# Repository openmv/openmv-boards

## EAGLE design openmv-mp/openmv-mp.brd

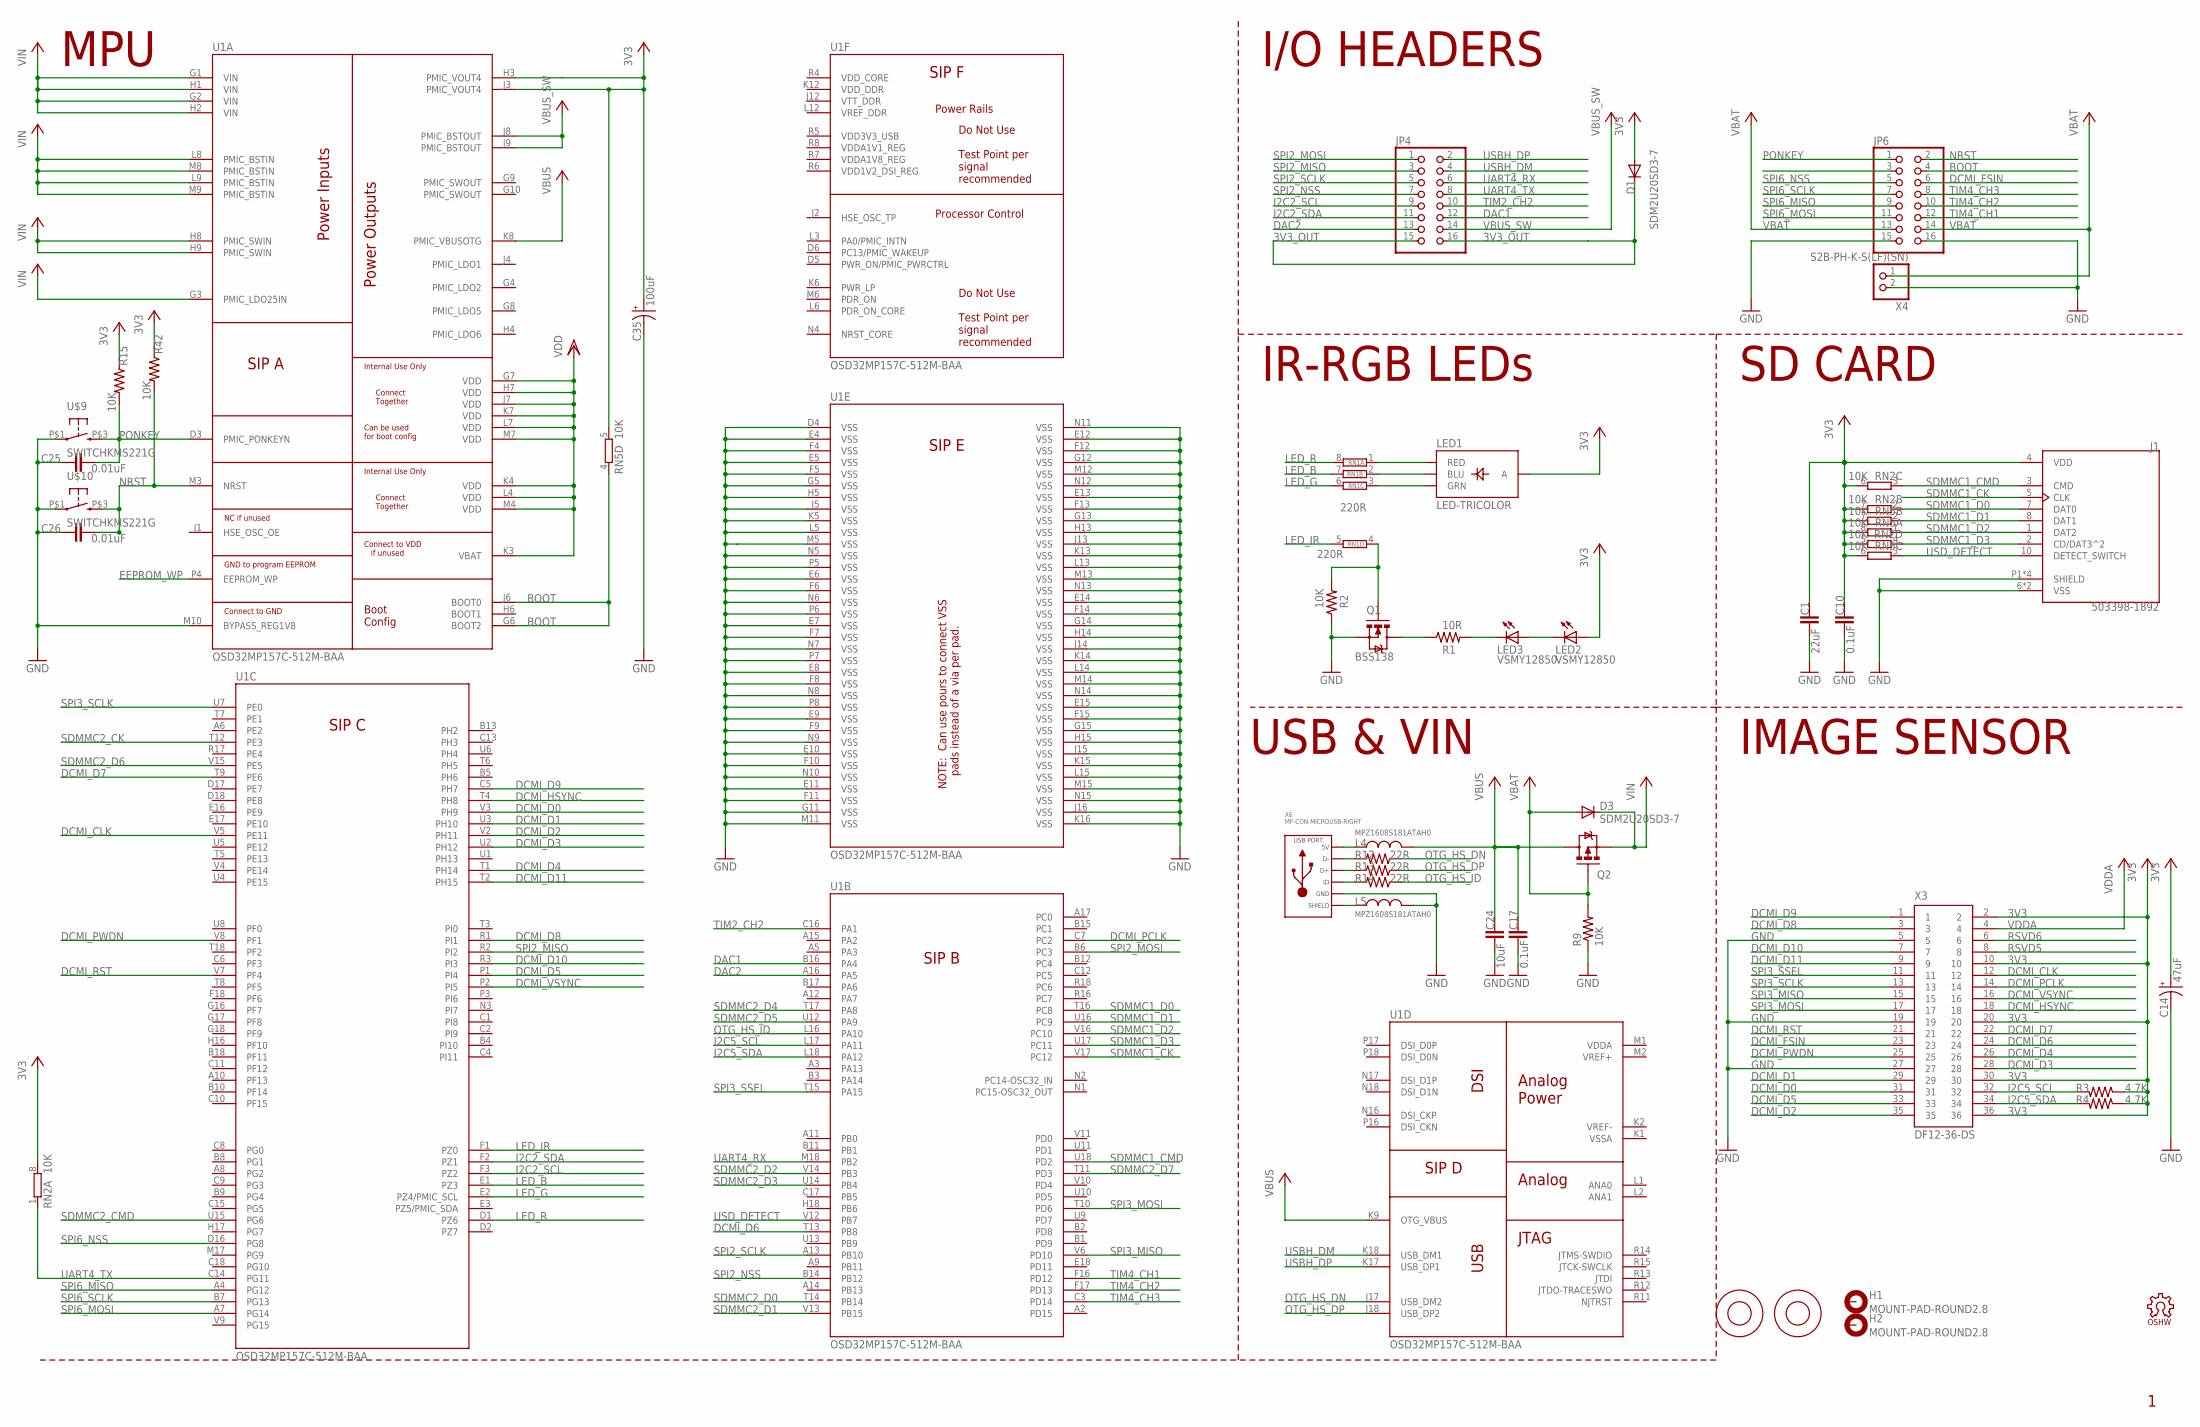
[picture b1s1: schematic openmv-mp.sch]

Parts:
C1: 22uF; 0805
C10, C17: 0.1uF; 0402-CAP
C14: 47uF; EIA3216
C24: 10uF; 0402-CAP
C25, C26: 0.01uF; 0402-CAP
C35: 100uF; EIA3216
D1, D3: SDM2U20SD3-7; SOD-323
H1, H2: MOUNT-PAD-ROUND2.8; 2,8-PAD
J1: 503398-1892; MOLEX_503398-1892
JP4, JP6: PINHD-2X8; 2X08
L4, L5: MPZ1608S181ATAH0; C0402
LED1: LED-TRICOLOR; LED-TRICOLOR-SMD-MF
LED2, LED3: VSMY12850; LED-1206
LOGO1: OSHW_LOGO_FILLX0100-NT; OSHW_FILLX100_NOTEXT
M1, M2: 9774030243R; 9774030151R
Q1: BSS138; SOT23-3
Q2: Si2301BDS; SOT23-3
R1: 10R; 0402-RES
R2, R9, R15, R42: 10K; 0402-RES
R3, R4: 4.7K; 0402-RES
R12, R13, R14: 22R; 0402-RES
RN1: 220R; EXBV8V
RN2, RN5: 10K; EXBV8V
U1: OSD32MP157C-512M-BAA; OSD32MP15X-BGA-324
U$9, U$10: SWITCHKMS221G; KMS221G
X3: DF12-36-DS
X4: S2B-PH-K-S(LF)(SN); JST-PH-2-THM-RA
X6: MF-CON-MICROUSB-RIGHT; MICROUSB-RIGHT

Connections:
3V3: C1.1, C10.1, C14.A (+), C35.A (+), D1.2 (A), J1.4 (VDD), LED1.A, LED2.A, R3.1, R4.1, R15.1, R42.1, RN2.5 (2), RN2.6 (2), RN2.7 (2), RN2.8 (2), RN5.5 (2), RN5.6 (2), RN5.7 (2), RN5.8 (2), U1.H3 (PMIC_VOUT4), U1.J3 (PMIC_VOUT4), X3.2, X3.10, X3.20, X3.30, X3.36
3V3_OUT: D1.1 (C), JP4.15, JP4.16
BOOT: JP6.4, RN5.4 (1), U1.G6 (BOOT2), U1.J6 (BOOT0)
DAC1: JP4.12, U1.B16 (PA4)
DAC2: JP4.13, U1.A16 (PA5)
DCMI_CLK: U1.V5 (PE11), X3.12
DCMI_D0: U1.V3 (PH9), X3.31
DCMI_D1: U1.U3 (PH10), X3.29
DCMI_D2: U1.V2 (PH11), X3.35
DCMI_D3: U1.U2 (PH12), X3.28
DCMI_D4: U1.T1 (PH14), X3.26
DCMI_D5: U1.P1 (PI4), X3.33
DCMI_D6: U1.T13 (PB8), X3.24
DCMI_D7: U1.T9 (PE6), X3.22
DCMI_D8: U1.R1 (PI1), X3.3
DCMI_D9: U1.C5 (PH7), X3.1
DCMI_D10: U1.R3 (PI3), X3.7
DCMI_D11: U1.T2 (PH15), X3.9
DCMI_FSIN: JP6.6, X3.23
DCMI_HSYNC: U1.T4 (PH8), X3.18
DCMI_PCLK: U1.C7 (PC2), X3.14
DCMI_PWDN: U1.V8 (PF1), X3.25
DCMI_RST: U1.V7 (PF4), X3.21
DCMI_VSYNC: U1.P2 (PI5), X3.16
EEPROM_WP: U1.P4 (EEPROM_WP)
GND: C1.2, C10.2, C14.C (-), C17.2, C24.2, C25.2, C26.2, C35.C (-), J1.6 (VSS), J1.9 (VSS), J1.P1 (SHIELD), J1.P2 (SHIELD), J1.P3 (SHIELD), J1.P4 (SHIELD), JP6.15, JP6.16, L5.2, Q1.2 (S), R2.1, R9.1, U1.D4 (VSS), U1.E4 (VSS), U1.E5 (VSS), U1.E6 (VSS), U1.E7 (VSS), U1.E8 (VSS), U1.E9 (VSS), U1.E10 (VSS), U1.E11 (VSS), U1.E12 (VSS), U1.E13 (VSS), U1.E14 (VSS), U1.E15 (VSS), U1.F4 (VSS), U1.F5 (VSS), U1.F6 (VSS), U1.F7 (VSS), U1.F8 (VSS), U1.F9 (VSS), U1.F10 (VSS), U1.F11 (VSS), U1.F12 (VSS), U1.F13 (VSS), U1.F14 (VSS), U1.F15 (VSS), U1.G5 (VSS), U1.G11 (VSS), U1.G12 (VSS), U1.G13 (VSS), U1.G14 (VSS), U1.G15 (VSS), U1.H5 (VSS), U1.H13 (VSS), U1.H14 (VSS), U1.H15 (VSS), U1.J5 (VSS), U1.J13 (VSS), U1.J14 (VSS), U1.J15 (VSS), U1.J16 (VSS), U1.K5 (VSS), U1.K13 (VSS), U1.K14 (VSS), U1.K15 (VSS), U1.K16 (VSS), U1.L5 (VSS), U1.L13 (VSS), U1.L14 (VSS), U1.L15 (VSS), U1.M5 (VSS), U1.M10 (BYPASS_REG1V8), U1.M11 (VSS), U1.M12 (VSS), U1.M13 (VSS), U1.M14 (VSS), U1.M15 (VSS), U1.N5 (VSS), U1.N6 (VSS), U1.N7 (VSS), U1.N8 (VSS), U1.N9 (VSS), U1.N10 (VSS), U1.N11 (VSS), U1.N12 (VSS), U1.N13 (VSS), U1.N14 (VSS), U1.N15 (VSS), U1.P5 (VSS), U1.P6 (VSS), U1.P7 (VSS), U1.P8 (VSS), U$9.P$1 (1), U$10.P$1 (1), X3.5, X3.19, X3.27, X4.2 (1), X6.5 (GND)
I2C2_SCL: JP4.9, U1.F3 (PZ2)
I2C2_SDA: JP4.11, U1.F2 (PZ1)
I2C5_SCL: R3.2, U1.L17 (PA11), X3.32
I2C5_SDA: R4.2, U1.L18 (PA12), X3.34
LED_B: RN1.7 (2), U1.E1 (PZ3)
LED_G: RN1.6 (2), U1.E2 (PZ4/PMIC_SCL)
LED_IR: RN1.5 (2), U1.F1 (PZ0)
LED_R: RN1.8 (2), U1.D1 (PZ6)
unnamed: Q1.1 (G), R2.2, RN1.4 (1)
unnamed: LED1.B (BLU), RN1.2 (1)
unnamed: LED1.R (RED), RN1.1
unnamed: LED1.G (GRN), RN1.3 (1)
unnamed: LED3.C, R1.2
unnamed: Q1.3 (D), R1.1
unnamed: LED2.C, LED3.A
unnamed: L4.1, X6.1 (5V)
unnamed: R12.2, X6.2 (D-)
unnamed: R13.2, X6.3 (D+)
unnamed: R14.2, X6.4 (ID)
unnamed: L5.1, X6.S1 (SLD), X6.S2 (SLD), X6.S3 (SLD), X6.S4 (SLD), X6.S5 (SLD), X6.S6 (SLD)
NRST: C26.1, JP6.2, R42.2, U1.M3 (NRST), U$10.P$3 (2)
OTG_HS_DN: R12.1, U1.J17 (USB_DM2)
OTG_HS_DP: R13.1, U1.J18 (USB_DP2)
OTG_HS_ID: R14.1, U1.L16 (PA10)
PONKEY: C25.1, JP6.1, R15.2, U1.D3 (PMIC_PONKEYN), U$9.P$3 (2)
RSVD5: X3.8
RSVD6: X3.6
SDMMC1_CK: J1.5 (CLK), U1.V17 (PC12)
SDMMC1_CMD: J1.3 (CMD), RN2.3 (1), U1.U18 (PD2)
SDMMC1_D0: J1.7 (DAT0), RN2.2 (1), U1.T16 (PC8)
SDMMC1_D1: J1.8 (DAT1), RN5.2 (1), U1.U16 (PC9)
SDMMC1_D2: J1.1 (DAT2), RN5.1, U1.V16 (PC10)
SDMMC1_D3: J1.2 (CD/DAT3^2), RN2.4 (1), U1.U17 (PC11)
SDMMC2_CK: U1.T12 (PE3)
SDMMC2_CMD: U1.U15 (PG6)
SDMMC2_D0: U1.T14 (PB14)
SDMMC2_D1: U1.V13 (PB15)
SDMMC2_D2: U1.V14 (PB3)
SDMMC2_D3: U1.U14 (PB4)
SDMMC2_D4: U1.T17 (PA8)
SDMMC2_D5: U1.U12 (PA9)
SDMMC2_D6: U1.V15 (PE5)
SDMMC2_D7: U1.T11 (PD3)
SPI2_MISO: JP4.3, U1.R2 (PI2)
SPI2_MOSI: JP4.1, U1.B6 (PC3)
SPI2_NSS: JP4.7, U1.B14 (PB12)
SPI2_SCLK: JP4.5, U1.A13 (PB10)
SPI3_MISO: U1.V6 (PD10), X3.15
SPI3_MOSI: U1.T10 (PD6), X3.17
SPI3_SCLK: U1.U7 (PE0), X3.13
SPI3_SSEL: U1.T15 (PA15), X3.11
SPI6_MISO: JP6.9, U1.A4 (PG12)
SPI6_MOSI: JP6.11, U1.A7 (PG14)
SPI6_NSS: JP6.5, U1.D16 (PG8)
SPI6_SCLK: JP6.7, U1.B7 (PG13)
TIM2_CH2: JP4.10, U1.C16 (PA1)
TIM4_CH1: JP6.12, U1.F16 (PD12)
TIM4_CH2: JP6.10, U1.F17 (PD13)
TIM4_CH3: JP6.8, U1.C3 (PD14)
UART4_RX: JP4.6, U1.M18 (PB2)
UART4_TX: JP4.8, RN2.1, U1.C14 (PG11)
USBH_DM: JP4.4, U1.K18 (USB_DM1)
USBH_DP: JP4.2, U1.K17 (USB_DP1)
USD_DETECT: J1.10 (DETECT_SWITCH), RN5.3 (1), U1.V12 (PB7)
VBAT: D3.2 (A), JP6.13, JP6.14, Q2.1 (G), R9.2, X4.1 (2)
VBUS: C17.1, C24.1, L4.2, Q2.3 (D), U1.K8 (PMIC_VBUSOTG), U1.K9 (OTG_VBUS)
VBUS_SW: JP4.14, U1.J8 (PMIC_BSTOUT), U1.J9 (PMIC_BSTOUT)
VDD: U1.G7 (VDD), U1.H7 (VDD), U1.J7 (VDD), U1.K3 (VBAT), U1.K4 (VDD), U1.K7 (VDD), U1.L4 (VDD), U1.L7 (VDD), U1.M4 (VDD), U1.M7 (VDD)
VDDA: X3.4
VIN: D3.1 (C), Q2.2 (S), U1.G1 (VIN), U1.G2 (VIN), U1.G3 (PMIC_LDO25IN), U1.H1 (VIN), U1.H2 (VIN), U1.H8 (PMIC_SWIN), U1.H9 (PMIC_SWIN), U1.L8 (PMIC_BSTIN), U1.L9 (PMIC_BSTIN), U1.M8 (PMIC_BSTIN), U1.M9 (PMIC_BSTIN)

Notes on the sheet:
SD CARD
IMAGE SENSOR
IR-RGB LEDs
MPU
I/O HEADERS
USB & VIN

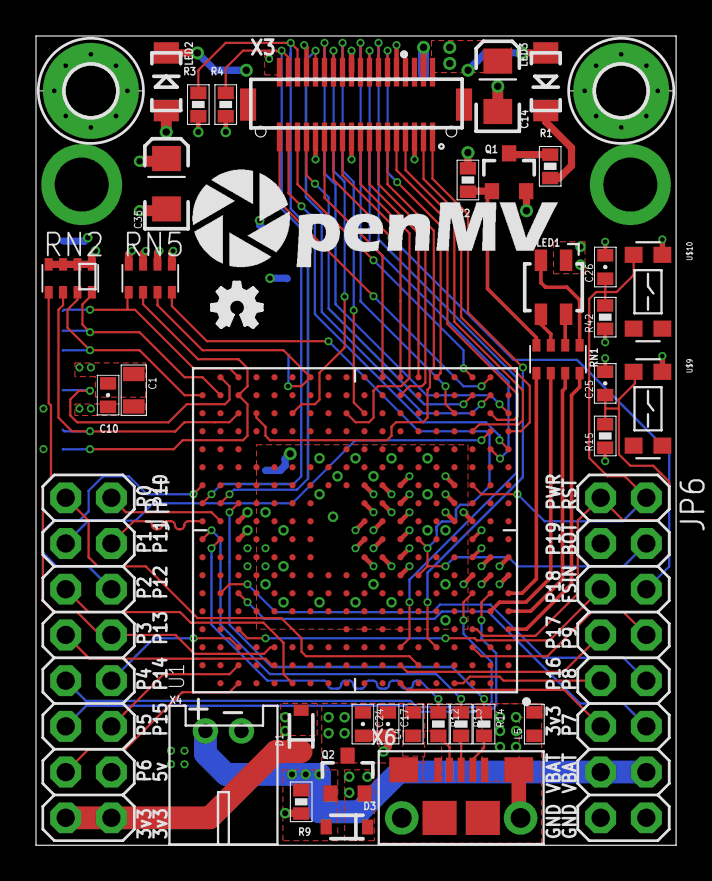
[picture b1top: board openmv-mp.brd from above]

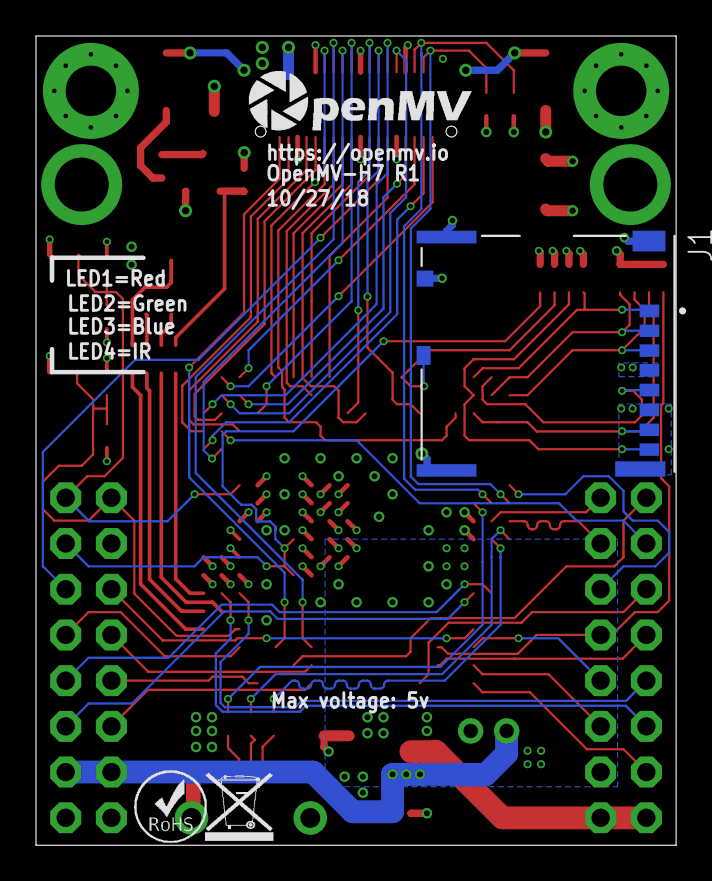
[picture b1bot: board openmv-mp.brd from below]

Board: 4 copper layers, 35.6 x 45.0 mm, 48 parts (4 on the bottom side), 82 nets.

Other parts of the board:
U$1: WEEE
U$2: ROHS
U$3: OMV-LOGO
U$6: OMV-LOGO-BIG

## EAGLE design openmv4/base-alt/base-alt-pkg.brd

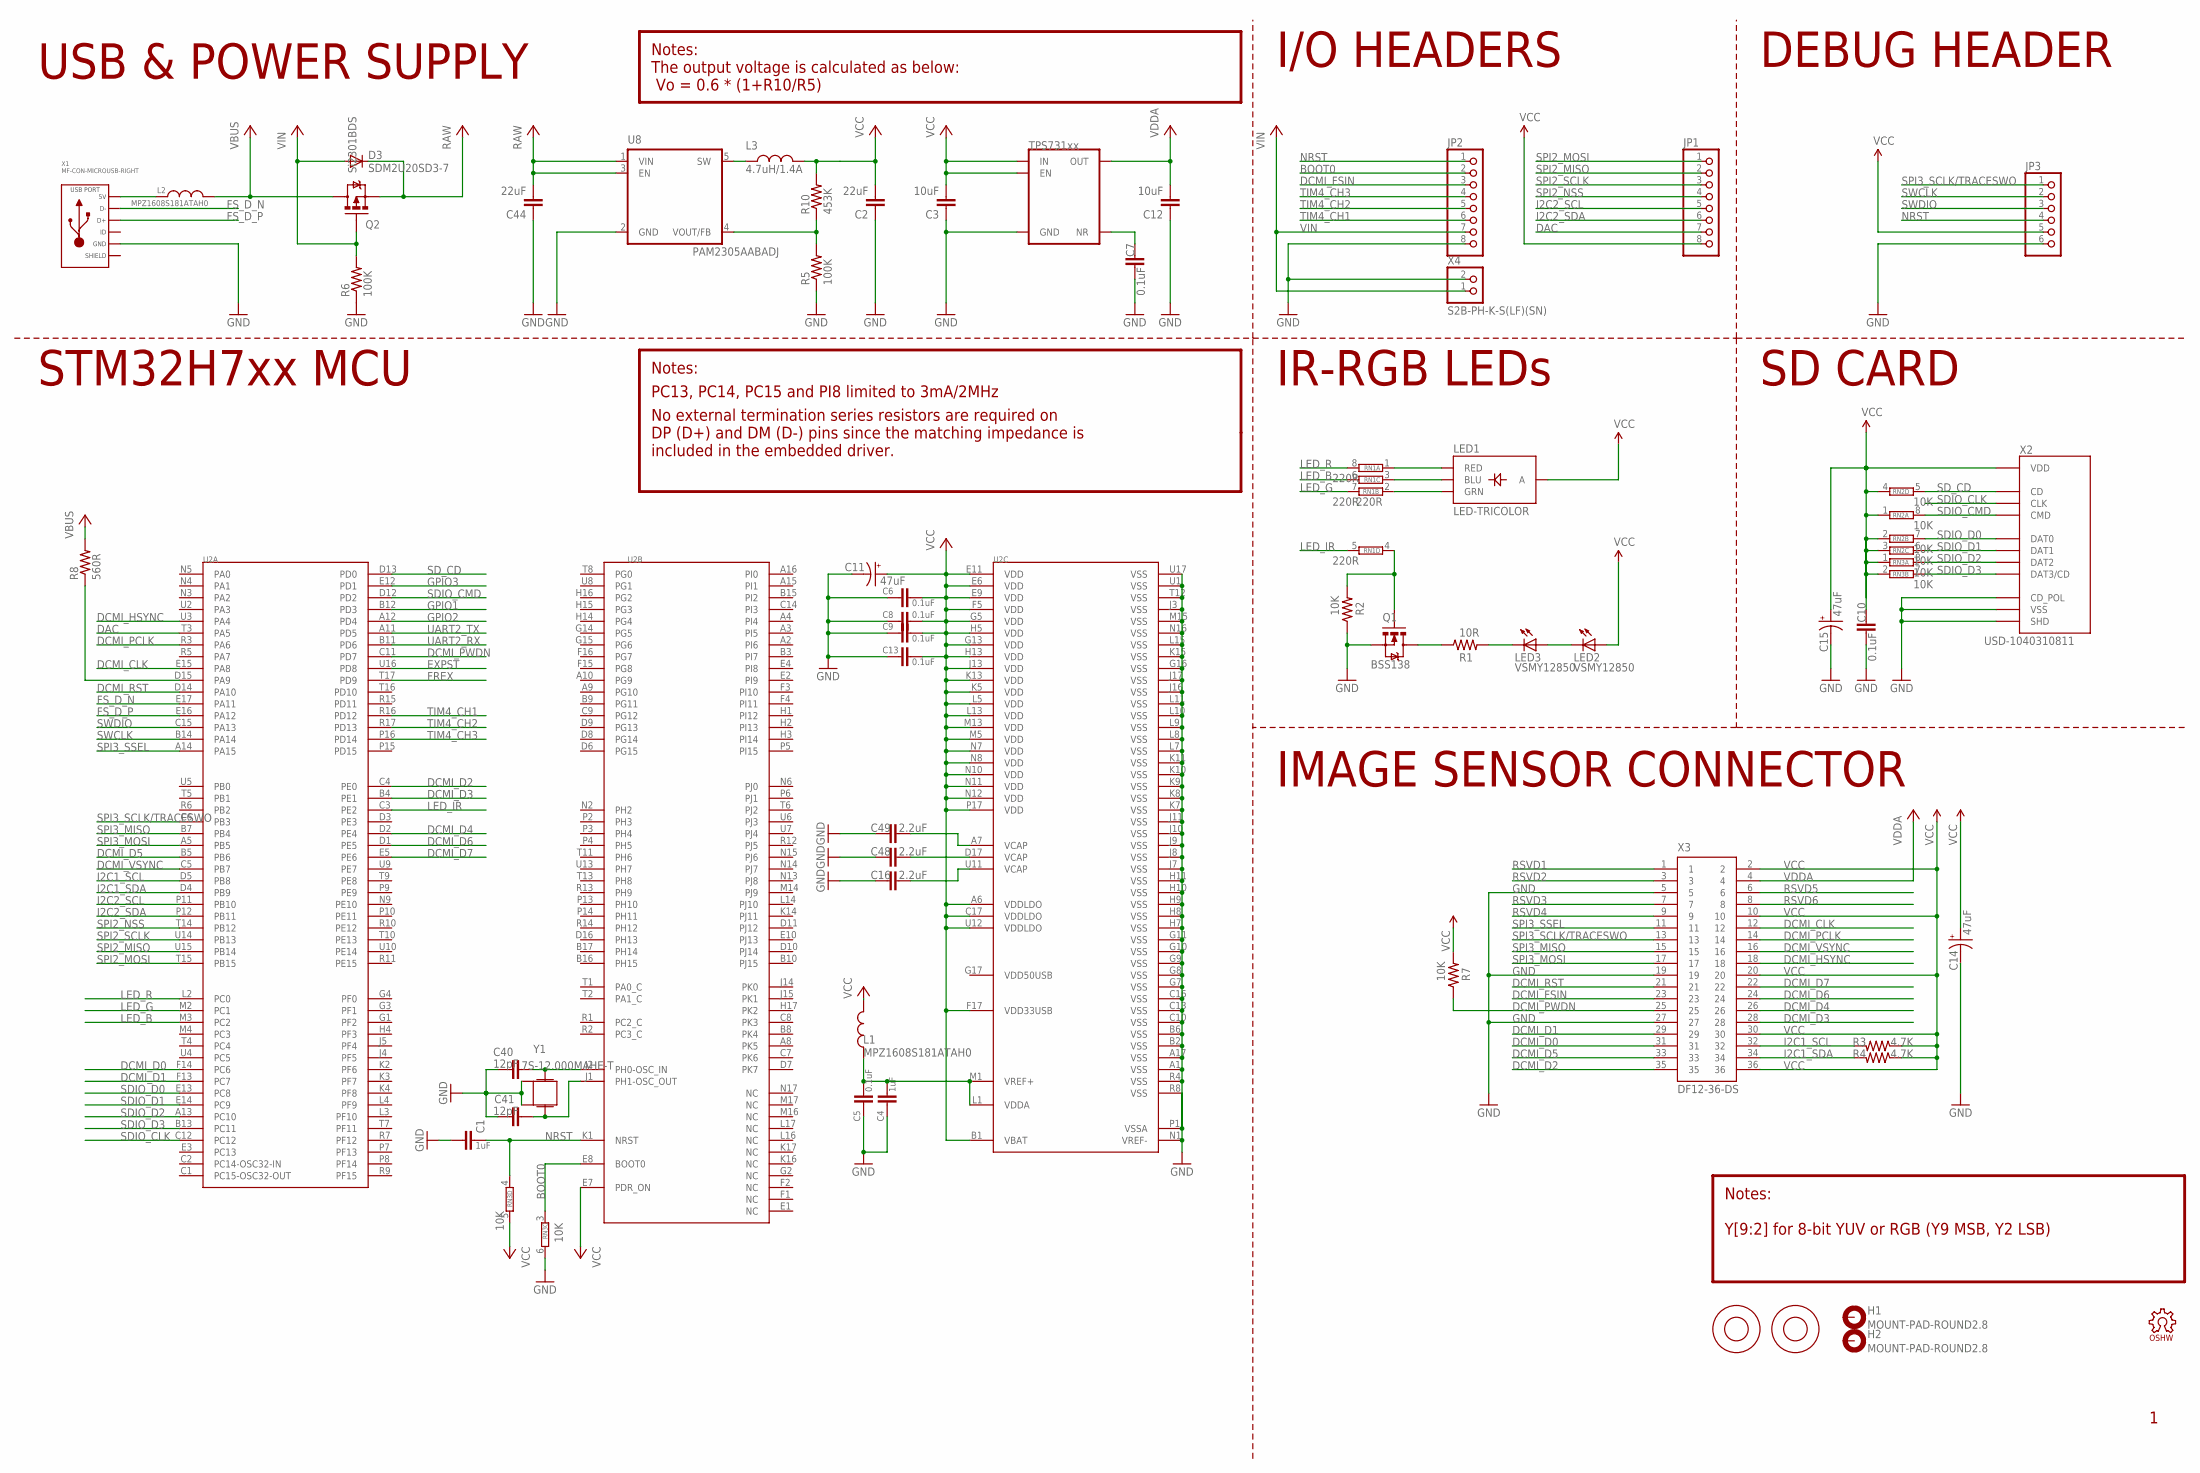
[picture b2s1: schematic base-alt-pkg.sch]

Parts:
C1, C4: 1uF; 0603-CAP
C2, C44: 22uF; 0805
C3, C12: 10uF; 0805
C5, C6, C7, C8, C9, C10, C13: 0.1uF; 0603-CAP
C11, C14, C15: 47uF; EIA3216
C16, C48, C49: 2.2uF; 0603-CAP
C40, C41: 12pF; 0603-CAP
D3: SDM2U20SD3-7; SOD-323
H1, H2: MOUNT-PAD-ROUND2.8; 2,8-PAD
JP1, JP2: PINHD-1X8; 1X08
JP3: PINHD-1X6; 1X06
L1, L2: MPZ1608S181ATAH0; 0603
L3: 4.7uH/1.4A; 1007
LED1: LED-TRICOLOR; LED-TRICOLOR-SMD-MF
LED2, LED3: VSMY12850; LED-1206
LOGO1: OSHW_LOGO_FILLX0100-NT; OSHW_FILLX100_NOTEXT
M1, M2: 9774030243R; 9774030151R
Q1: BSS138; SOT23-3
Q2: Si2301BDS; SOT23-3
R1: 10R; 0603-RES
R2, R7: 10K; 0603-RES
R3, R4: 4.7K; 0603-RES
R5, R6: 100K; 0603-RES
R8: 560R; 0603-RES
R10: 453K; 0603-RES
RN1: 220R; EXBV8V
RN2, RN3: 10K; EXBV8V
U2: STM32H743XIH6; TFBGA240+25
U5: TPS731XX; SOT23-5
U8: PAM2305AABADJ; TSOT25
X1: MF-CON-MICROUSB-RIGHT; MICROUSB-RIGHT
X2: USD-1040310811; 1040310811
X3: DF12-36-DS
X4: S2B-PH-K-S(LF)(SN); JST-PH-2-THM-RA
Y1: 7S-12.000MAHE-T; CRYSTAL-2.5X2.0

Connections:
BOOT0: JP2.2, RN3.3 (1), U2.E8 (BOOT0)
DAC: JP1.7, U2.T3 (PA5)
DCMI_CLK: U2.E15 (PA8), X3.12
DCMI_D0: U2.F14 (PC6), X3.31
DCMI_D1: U2.F13 (PC7), X3.29
DCMI_D2: U2.C4 (PE0), X3.35
DCMI_D3: U2.B4 (PE1), X3.28
DCMI_D4: U2.D2 (PE4), X3.26
DCMI_D5: U2.B5 (PB6), X3.33
DCMI_D6: U2.D1 (PE5), X3.24
DCMI_D7: U2.E5 (PE6), X3.22
DCMI_FSIN: JP2.3, X3.23
DCMI_HSYNC: U2.U3 (PA4), X3.18
DCMI_PCLK: U2.R3 (PA6), X3.14
DCMI_PWDN: R7.1, U2.C11 (PD7), X3.25
DCMI_RST: U2.D14 (PA10), X3.21
DCMI_VSYNC: U2.C5 (PB7), X3.16
EXPST: U2.U16 (PD8)
FREX: U2.T17 (PD9)
FS_D_N: U2.E17 (PA11), X1.2 (D-)
FS_D_P: U2.E16 (PA12), X1.3 (D+)
GND: C1.2, C2.1, C3.1, C4.2, C5.2, C6.2, C7.2, C8.2, C9.2, C10.2, C11.C (-), C12.1, C13.2, C14.C (-), C15.C (-), C16.2, C40.1, C41.1, C44.1, C48.2, C49.2, JP2.8, JP3.6, Q1.2 (S), R2.1, R5.1, R6.1, RN3.6 (2), U2.A1 (VSS), U2.A17 (VSS), U2.B2 (VSS), U2.B6 (VSS), U2.C10 (VSS), U2.C13 (VSS), U2.C16 (VSS), U2.G7 (VSS), U2.G8 (VSS), U2.G9 (VSS), U2.G10 (VSS), U2.G11 (VSS), U2.G16 (VSS), U2.H7 (VSS), U2.H8 (VSS), U2.H9 (VSS), U2.H10 (VSS), U2.H11 (VSS), U2.J3 (VSS), U2.J7 (VSS), U2.J8 (VSS), U2.J9 (VSS), U2.J10 (VSS), U2.J11 (VSS), U2.J16 (VSS), U2.J17 (VSS), U2.K7 (VSS), U2.K8 (VSS), U2.K9 (VSS), U2.K10 (VSS), U2.K11 (VSS), U2.K15 (VSS), U2.L7 (VSS), U2.L8 (VSS), U2.L9 (VSS), U2.L10 (VSS), U2.L11 (VSS), U2.L15 (VSS), U2.M15 (VSS), U2.N1 (VREF-), U2.N16 (VSS), U2.P1 (VSSA), U2.R4 (VSS), U2.R8 (VSS), U2.T12 (VSS), U2.U1 (VSS), U2.U17 (VSS), U5.2 (GND), U8.2 (GND), X1.5 (GND), X2.CD$2 (CD_POL), X2.G$1 (SHD), X2.G$2 (SHD), X2.G$3 (SHD), X2.G$4 (SHD), X2.P$6 (VSS), X3.5, X3.19, X3.27, X4.2 (1), Y1.2, Y1.4
GPIO1: U2.B12 (PD3)
GPIO2: U2.A12 (PD4)
GPIO3: U2.E12 (PD1)
I2C1_SCL: R3.2, U2.D5 (PB8), X3.32
I2C1_SDA: R4.2, U2.D4 (PB9), X3.34
I2C2_SCL: JP1.5, U2.P11 (PB10)
I2C2_SDA: JP1.6, U2.P12 (PB11)
LED_B: RN1.6 (2), U2.M3 (PC2)
LED_G: RN1.7 (2), U2.M2 (PC1)
LED_IR: RN1.5 (2), U2.C3 (PE2)
LED_R: RN1.8 (2), U2.L2 (PC0)
unnamed: C40.2, U2.J2 (PH0-OSC_IN), Y1.3 (2)
unnamed: C41.2, U2.J1 (PH1-OSC_OUT), Y1.1
unnamed: Q1.1 (G), R2.2, RN1.4 (1)
unnamed: LED1.B (BLU), RN1.3 (1)
unnamed: L2.1, X1.1 (5V)
unnamed: LED1.R (RED), RN1.1
unnamed: LED1.G (GRN), RN1.2 (1)
unnamed: LED3.C, R1.2
unnamed: C7.1, U5.4 (NR)
unnamed: R5.2, R10.1, U8.4 (VOUT/FB)
unnamed: Q1.3 (D), R1.1
unnamed: LED2.C, LED3.A
unnamed: R8.1, U2.D15 (PA9)
unnamed: C4.1, C5.1, L1.1, U2.L1 (VDDA), U2.M1 (VREF+)
unnamed: C49.1, U2.A7 (VCAP)
unnamed: C48.1, U2.D17 (VCAP)
unnamed: C16.1, U2.U11 (VCAP)
NRST: C1.1, JP2.1, JP3.4, RN3.4 (1), U2.K1 (NRST)
RAW: C44.2, D3.1 (C), Q2.2 (S), U8.1 (VIN), U8.3 (EN)
RSVD1: X3.1
RSVD2: X3.3
RSVD3: X3.7
RSVD4: X3.9
RSVD5: X3.6
RSVD6: X3.8
SDIO_CLK: U2.C12, X2.P$5 (CLK)
SDIO_CMD: RN2.8 (2), U2.D12 (PD2), X2.P$3 (CMD)
SDIO_D0: RN2.7 (2), U2.E13 (PC8), X2.P$7 (DAT0)
SDIO_D1: RN2.6 (2), U2.E14 (PC9), X2.P$8 (DAT1)
SDIO_D2: RN3.8 (2), U2.A13 (PC10), X2.P$1 (DAT2)
SDIO_D3: RN3.7 (2), U2.B13 (PC11), X2.P$2 (DAT3/CD)
SD_CD: RN2.5 (2), U2.D13 (PD0), X2.CD$1 (CD)
SPI2_MISO: JP1.2, U2.U15 (PB14)
SPI2_MOSI: JP1.1, U2.T15 (PB15)
SPI2_NSS: JP1.4, U2.T14 (PB12)
SPI2_SCLK: JP1.3, U2.U14 (PB13)
SPI3_MISO: U2.B7 (PB4), X3.15
SPI3_MOSI: U2.A5 (PB5), X3.17
SPI3_SCLK/TRACESWO: JP3.1, U2.C6 (PB3), X3.13
SPI3_SSEL: U2.A14 (PA15), X3.11
SW: L3.1, U8.5 (SW)
SWCLK: JP3.2, U2.B14 (PA14)
SWDIO: JP3.3, U2.C15 (PA13)
TIM4_CH1: JP2.6, U2.R16 (PD12)
TIM4_CH2: JP2.5, U2.R17 (PD13)
TIM4_CH3: JP2.4, U2.P16 (PD14)
UART2_RX: U2.B11 (PD6)
UART2_TX: U2.A11 (PD5)
VBUS: L2.2, Q2.3 (D), R8.2
VCC: C2.2, C3.2, C6.1, C8.1, C9.1, C10.1, C11.A (+), C13.1, C14.A (+), C15.A (+), JP1.8, JP3.5, L1.2, L3.2, LED1.A, LED2.A, R3.1, R4.1, R7.2, R10.2, RN2.1, RN2.2 (1), RN2.3 (1), RN2.4 (1), RN3.1, RN3.2 (1), RN3.5 (2), U2.A6 (VDDLDO), U2.B1 (VBAT), U2.C17 (VDDLDO), U2.E6 (VDD), U2.E7 (PDR_ON), U2.E9 (VDD), U2.E11 (VDD), U2.F5 (VDD), U2.F17 (VDD33USB), U2.G5 (VDD), U2.G13 (VDD), U2.H5 (VDD), U2.H13 (VDD), U2.J13 (VDD), U2.K5 (VDD), U2.K13 (VDD), U2.L5 (VDD), U2.L13 (VDD), U2.M5 (VDD), U2.M13 (VDD), U2.N7 (VDD), U2.N8 (VDD), U2.N10 (VDD), U2.N11 (VDD), U2.N12 (VDD), U2.P17 (VDD), U2.U12 (VDDLDO), U5.1 (IN), U5.3 (EN), X2.P$4 (VDD), X3.2, X3.10, X3.20, X3.30, X3.36
VDDA: C12.2, U5.5 (OUT), X3.4
VIN: D3.2 (A), JP2.7, Q2.1 (G), R6.2, X4.1 (2)

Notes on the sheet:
PC13, PC14, PC15 and PI8 limited to 3mA/2MHz
SD CARD
Y[9:2] for 8-bit YUV or RGB (Y9 MSB, Y2 LSB)
Notes:
IMAGE SENSOR CONNECTOR
STM32H7xx MCU
IR-RGB LEDs
USB & POWER SUPPLY
DEBUG HEADER
I/O HEADERS
No external termination series resistors are required on DP (D+) and DM (D-) pins since the matching impedance is included in the embedded driver.
The output voltage is calculated as below: Vo = 0.6 * (1+R10/R5)

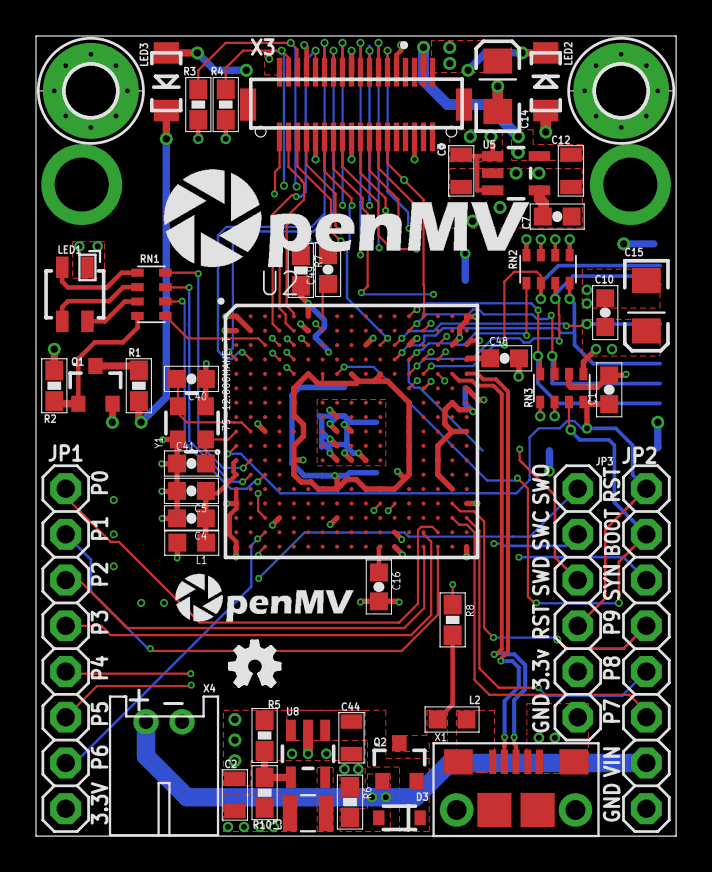
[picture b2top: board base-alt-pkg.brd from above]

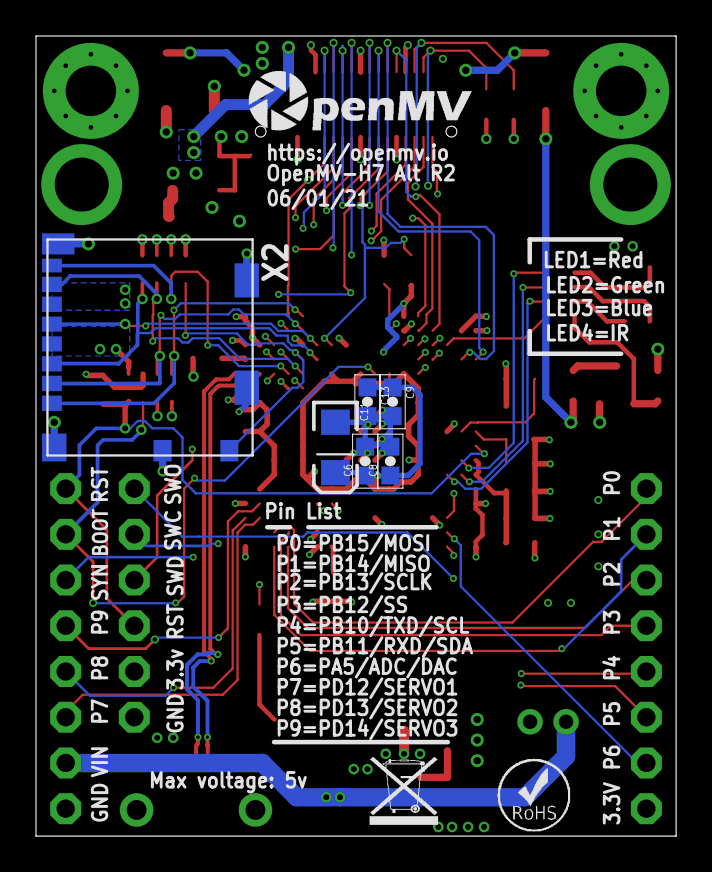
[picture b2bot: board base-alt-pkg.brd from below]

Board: 4 copper layers, 35.6 x 44.5 mm, 63 parts (9 on the bottom side), 72 nets.

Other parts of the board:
U$1: WEEE
U$2: ROHS
U$3: OMV-LOGO
U$4: OMV-LOGO-SMALL
U$6: OMV-LOGO-BIG

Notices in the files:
openmv-mp/openmv-mp.sch:
Copyright (c) 2018 OpenMV
openmv4/base-alt/base-alt-pkg.sch:
Copyright (c) 2021 OpenMV
parts and their libraries:
SparkFun-Aesthetics: Licensing: Creative Commons ShareAlike 4.0 International - https://creativecommons.org/licenses/by-sa/4.0
